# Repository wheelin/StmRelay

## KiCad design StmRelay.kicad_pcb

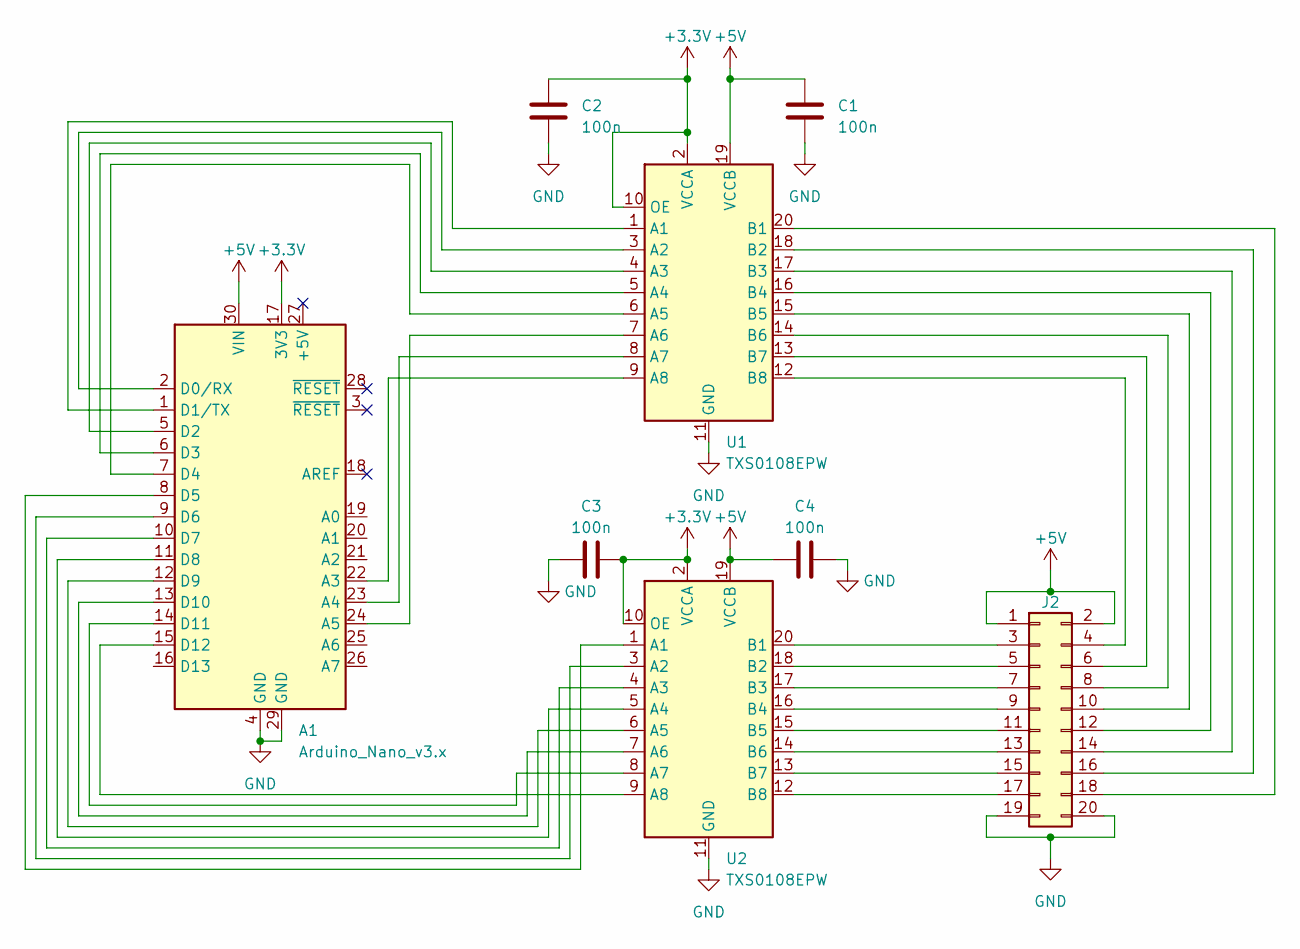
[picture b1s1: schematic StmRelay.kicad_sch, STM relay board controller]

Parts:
A1: Arduino_Nano_v3.x; Arduino_Nano
C1, C2, C3, C4: 100n; C_0603_1608Metric_Pad1.08x0.95mm_HandSolder
J2: Conn_02x10_Odd_Even; PinHeader_2x10_P2.54mm_Vertical
U1, U2: TXS0108EPW; TSSOP-20_4.4x6.5mm_P0.65mm

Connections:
+3.3V: A1.17 (3V3), C2.1, C3.2, U1.2 (VCCA), U1.10 (OE), U2.2 (VCCA), U2.10 (OE)
+5V: A1.30 (VIN), C1.1, C4.1, J2.1, J2.2, U1.19 (VCCB), U2.19 (VCCB)
GND: A1.4 (GND), A1.29 (GND), C1.2, C2.2, C3.1, C4.2, J2.19, J2.20, U1.11 (GND), U2.11 (GND)
unnamed: A1.22 (A3), U1.9 (A8)
unnamed: A1.23 (A4), U1.8 (A7)
unnamed: A1.24 (A5), U1.7 (A6)
unnamed: A1.2 (D0/RX), U1.3 (A2)
unnamed: A1.1 (D1/TX), U1.1 (A1)
unnamed: A1.5 (D2), U1.4 (A3)
unnamed: A1.6 (D3), U1.5 (A4)
unnamed: A1.7 (D4), U1.6 (A5)
unnamed: A1.8 (D5), U2.1 (A1)
unnamed: A1.9 (D6), U2.3 (A2)
unnamed: A1.10 (D7), U2.4 (A3)
unnamed: A1.11 (D8), U2.5 (A4)
unnamed: A1.12 (D9), U2.6 (A5)
unnamed: A1.13 (D10), U2.7 (A6)
unnamed: A1.14 (D11), U2.8 (A7)
unnamed: A1.15 (D12), U2.9 (A8)
unnamed: J2.3, U2.20 (B1)
unnamed: J2.4, U1.12 (B8)
unnamed: J2.5, U2.18 (B2)
unnamed: J2.6, U1.13 (B7)
unnamed: J2.7, U2.17 (B3)
unnamed: J2.8, U1.14 (B6)
unnamed: J2.9, U2.16 (B4)
unnamed: J2.10, U1.15 (B5)
unnamed: J2.11, U2.15 (B5)
unnamed: J2.12, U1.16 (B4)
unnamed: J2.13, U2.14 (B6)
unnamed: J2.14, U1.17 (B3)
unnamed: J2.15, U2.13 (B7)
unnamed: J2.16, U1.18 (B2)
unnamed: J2.17, U2.12 (B8)
unnamed: J2.18, U1.20 (B1)

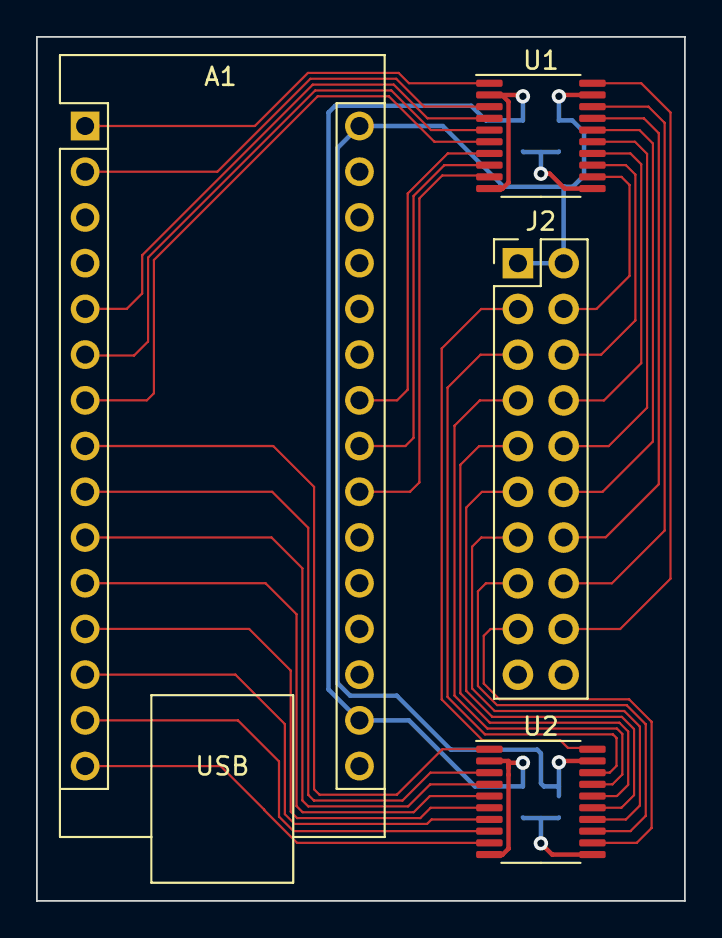
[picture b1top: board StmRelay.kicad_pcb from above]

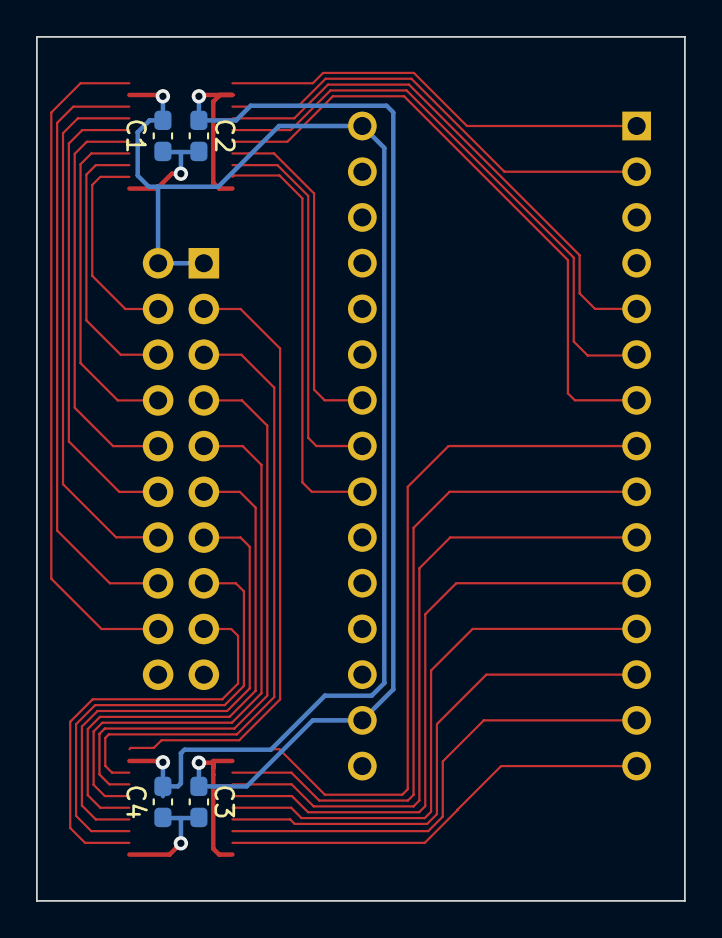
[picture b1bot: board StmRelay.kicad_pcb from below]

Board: 4 copper layers, 36.0 x 48.0 mm, 8 parts (4 on the bottom side), 35 nets.

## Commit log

2023-03-11 first commit, board already ordered
2023-05-03 last modifs before shipping
